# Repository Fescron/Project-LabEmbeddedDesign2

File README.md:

# Project-LabEmbeddedDesign2

<br/>

This repository contains the **presentation**, **reports** and **code** for the project constructed for **Embedded System Design 2 - Lab**.

<br/>

## 1 - Quick links

- [**Reports and presentation**](documentation/reports)
- [General important Doxygen documentation](https://fescron.github.io/Project-LabEmbeddedDesign2/index.html)
- [Doxygen code documentation of individual files and methods](https://fescron.github.io/Project-LabEmbeddedDesign2/files.html)
- [Code for the custom TTN decoder](software/decoder.js)
- [Schematic of custom PCB](documentation/schematics/project-embeddedSystemDesign2.pdf)
- [Schematic of DRAMCO LoRaWAN shield](documentation/schematics/dramco-LoRa-addon-schematic-v4-0.pdf)
- [Picture with PCB dimensions](hardware/project-embeddedSystemDesign2/3d-renders/project-embeddedSystemDesign2-pcb-dimensions.png)
- [The Things Network - Applications](https://console.thethingsnetwork.org/applications/)
- [Cayenne Dashboard](https://cayenne.mydevices.com/cayenne/dashboard/start)

<br/>

## 2 - GIT repo structure

|  Location  |  Content  |
| ---------- | --------- |
| [/docs/](https://fescron.github.io/Project-LabEmbeddedDesign2/index.html) | **[Doxygen](http://www.doxygen.org) code documentation.** |
| <br/>      |           |
| [/documentation/current measurements/](documentation/current%20measurements) | Documents containing current measurements. |
| [/documentation/current measurements/measurements-SF/](documentation/current%20measurements/measurements-SF) | Pictures depicting current profiles for sending 6 measurements at full gain with different LoraWAN *Spreading Factors*. More information can be found in section *"3 - LoRaWAN spreading factor (RN2483)"* in [this](documentation/current%20measurements/currents-2-projectEmbeddedDesign2.pdf) file . |
| <br/>      |           |
| [/documentation/datasheets/](documentation/datasheets) | General datasheets regarding the used items. |
| [/documentation/datasheets/hardware-design/](documentation/datasheets/hardware-design) | Documents regarding hardware design for the `EFM32HG` microcontroller. |
| [/documentation/datasheets/timers-energy-rtc/](documentation/datasheets/timers-energy-rtc) | Documents regarding `timers`, the `RTC` and `energy modes` on the `EFM32HG` microcontroller. |
| <br/>      |           |
| [/documentation/figures/](documentation/figures) | Figures used in reports and the README. |
| [/documentation/figures/installation/](documentation/figures/installation) | **Pictures taken during the project installation.** |
| [/documentation/reports/](documentation/reports) | **Reports and presentation.** |
| [/documentation/schematics/](documentation/schematics) | Schematics. <br/>  See [this](documentation/schematics/project-embeddedSystemDesign2.pdf) file for the schematic of the *self designed PCB* and [this](documentation/schematics/dramco-LoRa-addon-schematic-v4-0.pdf) file for the schematic of the *DRAMCO LoRaWAN shield*.
| <br/>      |           |
| [/hardware/project-embeddedSystemDesign2/](hardware/project-embeddedSystemDesign2) | [KiCad](http://kicad-pcb.org/) PCB design files. <br/> See [this](hardware/project-embeddedSystemDesign2/pdf/project-embeddedSystemDesign2.pdf) file for the *schematic* and [this](hardware/project-embeddedSystemDesign2/bom/bom-custom-gecko-v1-0.pdf) file for the *BOM*. |
| [/hardware/project-embeddedSystemDesign2/3d-renders/](hardware/project-embeddedSystemDesign2/3d-renders) | Pictures of 3D renders of the *self designed PCB*. <br/> On [this](hardware/project-embeddedSystemDesign2/3d-renders/project-embeddedSystemDesign2-pcb-dimensions.png) picture the *dimensions* are displayed. <br/>  [This](hardware/project-embeddedSystemDesign2/3d-renders/project-embeddedSystemDesign2.png) is a render of the *front* and [this](hardware/project-embeddedSystemDesign2/3d-renders/project-embeddedSystemDesign2-back.png) is a render of the *back*. |
| <br/>      |           |
| [/software/EFM32HG-Embedded2-project/](software/EFM32HG-Embedded2-project) | **Code for the project.** <br/> See [this](https://fescron.github.io/Project-LabEmbeddedDesign2/index.html) page for *general important documentation* and [this](https://fescron.github.io/Project-LabEmbeddedDesign2/files.html) page for information regarding *individual files and their methods*. [This](software/decoder.js) is the *decoder* for use on The *Things Network*. |

<br/>

## 3 - Code flow

**Note:** The code is developed using `Simplicity Studio v4` on `Ubuntu 18.04 LTS`. The code also has [dbprint](https://github.com/Fescron/dbprint) functionality.

**Extra notes on the flowchart:**

- **(\*1):** The following things get initialized:
    - Chip
    - GPIO wakeup (buttons & ADXL INT1)
    - ADC
    - Disable RN2483
    - Accelerometer (initialize SPI and use it to configure the accelerometer
- **(\*2):** On every external temperature measurement the VDD and DATA pin get re-configured. The oneWire protocol is achieved using *bit-banging*.
- **(\*3):** The RN2483 module gets enabled and configured before sending the data. Afterwards it gets disabled again. The **status** message is always send, measurements only if there are any recorded.
- **(\*4):** Only one set of measurements are send along with the status message.
- **(\*5):** The value of **X** depends on a configured setting.
- **(\*6):** A status message is send along with any recorded measurements.

<br/>

- Before entering a *sleep* state **all GPIO (data) pins are disabled** so they can't consume any power.
- **Clocks and peripherals** are only enabled when necessary.
- If an **error** occures this gets **forwarded to the cloud using a LoRaWAN status message**.
- To conserve sended bytes a **custom data-format** was used (along with a *decoder*).
- Negative internal and external temperatures were successfully send and displayed. The internal temperature seems to be 2 - 3 °C off.

<br/>

## 4 - Extra hardware changes

The [schematic](hardware/project-embeddedSystemDesign2/pdf/project-embeddedSystemDesign2.pdf) for the custom PCB **misses two resistors**. A surface mount `10 kΩ` resistor was added between the *data* and *power* pin for the DS18B20 temperature sensor. A `3,3 kΩ` resistor with wires was added between the `BREAK_1`pin and `VDD`. These added resistors can be seen on the bottom right on the left most picture below.

An **SMA connector for an external antenna** was also added to the DRAMCO LoRaWAN shield. This was done by **removing** the `chip-antenna`, capacitors `C3` and `C4` and inductor `L1` and replacing it with an SMA connector directly connected to the signal pin of the *RN2483* module. This modification can be seen on the right on the right most picture above.

To protect the PCB's from moisture and other contaminants, they were given 2 coats of `PLASTIK 70`.

<br/>

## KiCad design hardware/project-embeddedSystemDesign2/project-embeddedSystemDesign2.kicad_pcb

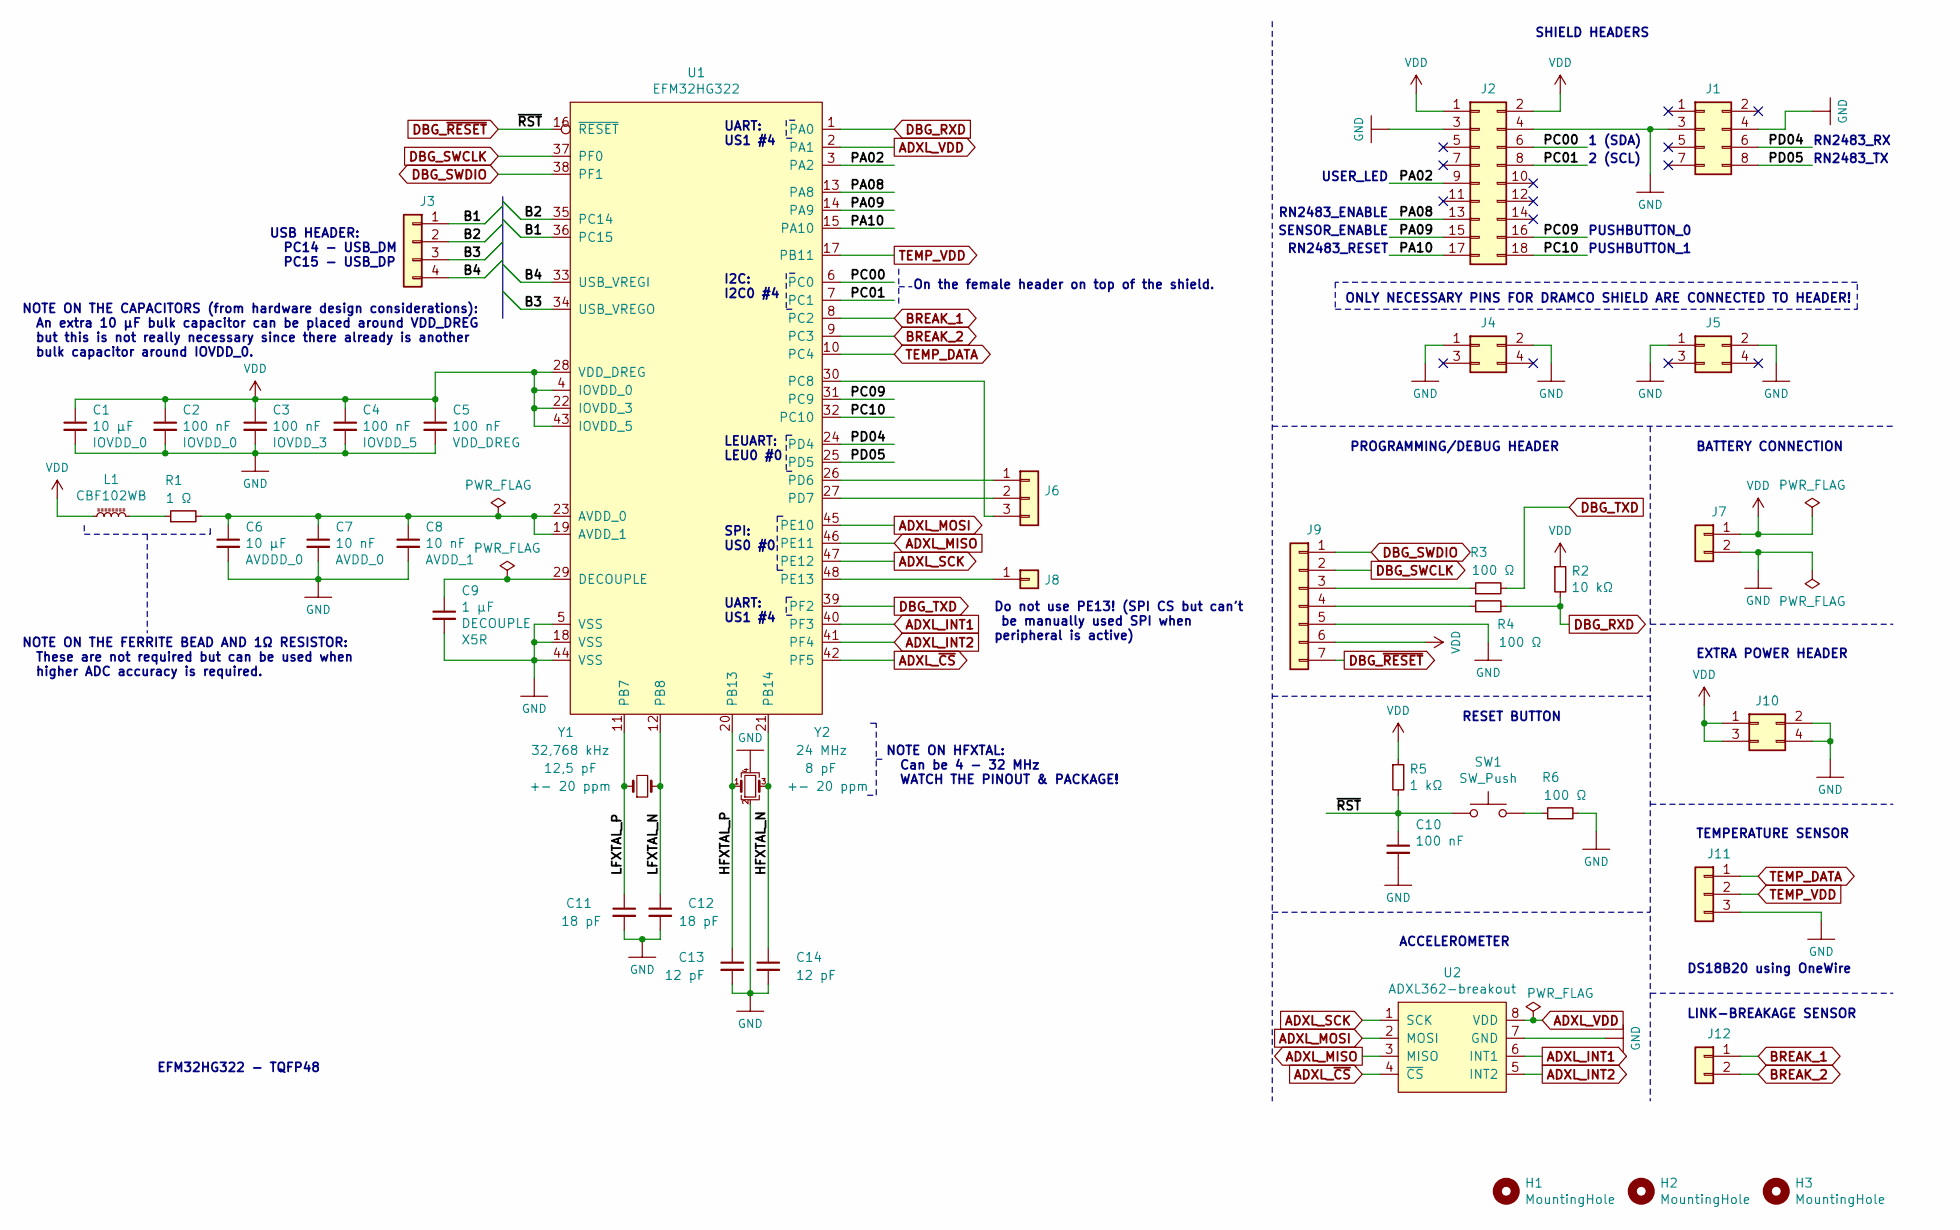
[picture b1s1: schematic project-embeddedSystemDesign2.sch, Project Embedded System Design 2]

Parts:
C1, C6: 10 µF; C_0805_2012Metric_Pad1.15x1.40mm_HandSolder
C2, C3, C4, C5, C10: 100 nF; C_0805_2012Metric_Pad1.15x1.40mm_HandSolder
C7, C8: 10 nF; C_0805_2012Metric_Pad1.15x1.40mm_HandSolder
C9: 1 µF; C_0805_2012Metric_Pad1.15x1.40mm_HandSolder
C11, C12: 18 pF; C_0805_2012Metric_Pad1.15x1.40mm_HandSolder
C13, C14: 12 pF; C_0805_2012Metric_Pad1.15x1.40mm_HandSolder
H1, H2, H3: MountingHole; MountingHole_3mm
J1: Conn_02x04_Odd_Even; PinHeader_2x04_P2.54mm_Vertical
J2: Conn_02x09_Odd_Even; PinHeader_2x09_P2.54mm_Vertical
J3: Conn_01x04; 1X04_LOCK
J4, J5: Conn_02x02_Odd_Even; PinHeader_2x02_P2.54mm_Vertical
J6, J11: Conn_01x03; 1X03_LOCK
J7: Conn_01x02; PinHeader_1x02_P2.54mm_Horizontal
J8: Conn_01x01; 1X01
J9: Conn_01x07; 1X07_LOCK
J10: Conn_02x02_Odd_Even; PinSocket_2x02_P2.54mm_Vertical
J12: Conn_01x02; 1X02_LOCK
L1: CBF102WB; L_0603_1608Metric_Pad1.05x0.95mm_HandSolder
R1: 1 Ω; R_0805_2012Metric_Pad1.15x1.40mm_HandSolder
R2: 10 kΩ; R_0805_2012Metric_Pad1.15x1.40mm_HandSolder
R3, R4, R6: 100 Ω; R_0805_2012Metric_Pad1.15x1.40mm_HandSolder
R5: 1 kΩ; R_0805_2012Metric_Pad1.15x1.40mm_HandSolder
SW1: SW_Push; SW_SPST_FSMSM
U1: EFM32HG322; LQFP-48_7x7mm_P0.5mm
U2: ADXL362-breakout; DIP-8_W10.16mm
Y1: 32,768 kHz; Crystal_SMD_2012-2Pin_2.0x1.2mm_HandSoldering; Tolerance +- 20 ppm
Y2: 24 MHz; CRYSTAL-SMD-5X3.2-4PAD; Tolerance +- 20 ppm

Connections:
/B1: J3.1, U1.36 (PC15)
/B2: J3.2, U1.35 (PC14)
/B3: J3.3, U1.34 (USB_VREGO)
/B4: J3.4, U1.33 (USB_VREGI)
/HFXTAL_N: C14.1, U1.21 (PB14), Y2.3
/HFXTAL_P: C13.1, U1.20 (PB13), Y2.1
/LFXTAL_N: C12.1, U1.12 (PB8), Y1.2
/LFXTAL_P: C11.1, U1.11 (PB7), Y1.1
/PA02: J2.9, U1.3 (PA2)
/PA08: J2.13, U1.13 (PA8)
/PA09: J2.15, U1.14 (PA9)
/PA10: J2.17, U1.15 (PA10)
/PC00: J2.6, U1.6 (PC0)
/PC01: J2.8, U1.7 (PC1)
/PC09: J2.16, U1.31 (PC9)
/PC10: J2.18, U1.32 (PC10)
/PD04: J1.6, U1.24 (PD4)
/PD05: J1.8, U1.25 (PD5)
ADXL_INT1: U1.40 (PF3), U2.6 (INT1)
ADXL_INT2: U1.41 (PF4), U2.5 (INT2)
ADXL_MISO: U1.46 (PE11), U2.3 (MISO)
ADXL_MOSI: U1.45 (PE10), U2.2 (MOSI)
ADXL_SCK: U1.47 (PE12), U2.1 (SCK)
ADXL_VDD: U1.2 (PA1), U2.8 (VDD)
ADXL_~CS: U1.42 (PF5), U2.4 (~CS)
BREAK_1: J12.1, U1.8 (PC2)
BREAK_2: J12.2, U1.9 (PC3)
DBG_RXD: R2.2, R4.2, U1.1 (PA0)
DBG_SWCLK: J9.2, U1.37 (PF0)
DBG_SWDIO: J9.1, U1.38 (PF1)
DBG_TXD: R3.2, U1.39 (PF2)
DBG_~RESET: C10.1, J9.7, R5.2, SW1.1, U1.16 (~RESET); also elsewhere on the board
GND: C1.2, C2.2, C3.2, C4.2, C5.2, C6.2, C7.2, C8.2, C9.2, C10.2, C11.2, C12.2, C13.2, C14.2, J1.3, J1.4, J2.3, J2.4, J4.1, J4.2, J5.1, J5.2, J7.2, J9.5, J10.2, J10.4, J11.3, R6.2, U1.5 (VSS), U1.18 (VSS), U1.44 (VSS), U2.7 (GND), Y2.2, Y2.4
unnamed: C6.1, C7.1, C8.1, R1.2, U1.19 (AVDD_1), U1.23 (AVDD_0)
unnamed: C9.1, U1.29 (DECOUPLE)
unnamed: J6.1, U1.26 (PD6)
unnamed: J6.2, U1.27 (PD7)
unnamed: J6.3, U1.30 (PC8)
unnamed: J8.1, U1.48 (PE13)
unnamed: J9.3, R3.1
unnamed: J9.4, R4.1
unnamed: L1.2, R1.1
unnamed 42: R6.1, SW1.2; also elsewhere on the board
TEMP_DATA: J11.1, U1.10 (PC4)
TEMP_VDD: J11.2, U1.17 (PB11)
VDD: C1.1, C2.1, C3.1, C4.1, C5.1, J2.1, J2.2, J7.1, J9.6, J10.1, J10.3, L1.1, R2.1, R5.1, U1.4 (IOVDD_0), U1.22 (IOVDD_3), U1.28 (VDD_DREG), U1.43 (IOVDD_5)

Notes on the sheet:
SHIELD HEADERS
PROGRAMMING/DEBUG HEADER
ACCELEROMETER
TEMPERATURE SENSOR
DS18B20 using OneWire
LINK-BREAKAGE SENSOR
RESET BUTTON
BATTERY CONNECTION
Do not use PE13! (SPI CS but can't be manually used SPI when peripheral is active)
EXTRA POWER HEADER
SPI: US0 #0
UART: US1 #4
I2C: I2C0 #4
LEUART: LEU0 #0
NOTE ON HFXTAL: Can be 4 - 32 MHz WATCH THE PINOUT & PACKAGE!
NOTE ON THE CAPACITORS (from hardware design considerations): An extra 10 µF bulk capacitor can be placed around VDD_DREG but this is not really necessary since there already is another bulk capacitor around IOVDD_0.
NOTE ON THE FERRITE BEAD AND 1Ω RESISTOR: These are not required but can be used when higher ADC accuracy is required.
EFM32HG322 - TQFP48
USB HEADER: PC14 - USB_DM PC15 - USB_DP
ONLY NECESSARY PINS FOR DRAMCO SHIELD ARE CONNECTED TO HEADER!
USER_LED
RN2483_ENABLE
SENSOR_ENABLE
RN2483_RESET
PUSHBUTTON_0
PUSHBUTTON_1
RN2483_RX
RN2483_TX
1 (SDA)
2 (SCL)
On the female header on top of the shield.

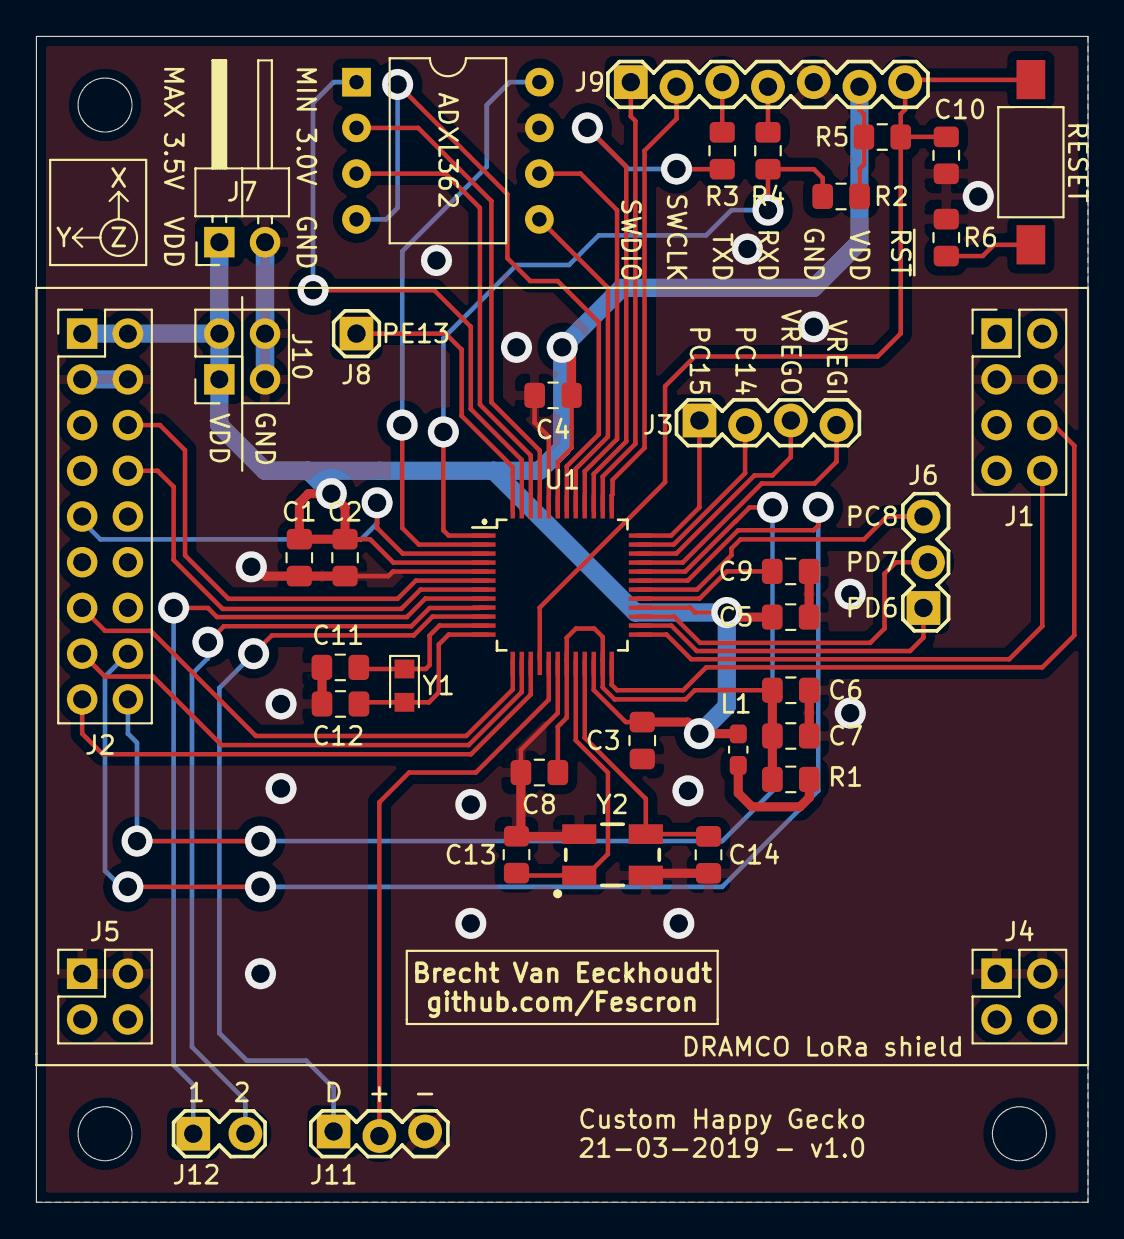
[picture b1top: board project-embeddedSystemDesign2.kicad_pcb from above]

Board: 2 copper layers, 58.4 x 64.8 mm, 41 parts (0 on the bottom side), 46 nets.

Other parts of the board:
RESET: SW_Push; SW_SPST_FSMSM

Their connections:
DBG_~RESET: RESET.1; also elsewhere on the board
unnamed 42: RESET.2; also elsewhere on the board

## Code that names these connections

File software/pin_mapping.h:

/***************************************************************************//**
 * @file pin_mapping.h
 * @brief The pin definitions for the custom Happy Gecko board.
 * @version 1.0
 * @author Brecht Van Eeckhoudt
 ******************************************************************************/


/* Include guards prevent multiple inclusions of the same header */
#ifndef _PIN_MAPPING_H_
#define _PIN_MAPPING_H_

#include <em_gpio.h>


/* ADXL362 */
#define ADXL_SPI            USART0
#define ADXL_SPI_LOC        0
#define ADXL_MOSI_PORT      gpioPortE
#define ADXL_MOSI_PIN       10
#define ADXL_MISO_PORT      gpioPortE
#define ADXL_MISO_PIN       11
#define ADXL_CLK_PORT       gpioPortE
#define ADXL_CLK_PIN        12
#define ADXL_NCS_PORT       gpioPortF 	/* Can't use the US0_CS port (PE13) to manually set/clear CS line */
#define ADXL_NCS_PIN        5

#define ADXL_INT1_PORT      gpioPortF
#define ADXL_INT1_PIN       3
#define ADXL_INT2_PORT      gpioPortF
#define ADXL_INT2_PIN       4
#define ADXL_VDD_PORT       gpioPortA
#define ADXL_VDD_PIN        1

/* LED */
#define LED_PORT            gpioPortA
#define LED_PIN             2

/* Buttons */
#define PB0_PORT            gpioPortC
#define PB0_PIN             9
#define PB1_PORT            gpioPortC
#define PB1_PIN             10

/* UART */
#define DBG_UART            USART1
#define DBG_UART_LOC        4
#define DBG_TXD_PORT        gpioPortF
#define DBG_TXD_PIN         2
#define DBG_RXD_PORT        gpioPortA
#define DBG_RXD_PIN         0

/* DS18B20 */
#define TEMP_DATA_PORT      gpioPortC
#define TEMP_DATA_PIN       4
#define TEMP_VDD_PORT       gpioPortB
#define TEMP_VDD_PIN        11

/* Link breakage sensor */
#define BREAK1_PORT         gpioPortC
#define BREAK1_PIN          2
#define BREAK2_PORT         gpioPortC
#define BREAK2_PIN          3

/* RN2483 */
#define RN2483_UART         LEUART0
#define RN2483_UART_LOC     0
#define RN2483_TX_PORT      gpioPortD
#define RN2483_TX_PIN       4
#define RN2483_RX_PORT      gpioPortD
#define RN2483_RX_PIN       5
#define RN2483_RESET_PORT   gpioPortA
#define RN2483_RESET_PIN    10

/* External header */
#define IIC_SDA_PORT        gpioPortC
#define IIC_SDA_PIN         0
#define IIC_SCL_PORT        gpioPortC
#define IIC_SCL_PIN         1

/* Power supply enable */
#define PM_RN2483_PORT		gpioPortA
#define PM_RN2483_PIN		8
#define PM_SENS_EXT_PORT	gpioPortA
#define PM_SENS_EXT_PIN		9


#endif /* _PIN_MAPPING_H_ */

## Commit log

2019-03-21 Add datasheets
2019-03-21 Change file structure
2019-03-22 Add PCB design files
2019-03-23 Update PCB
2019-03-23 Update BOM
2019-03-23 Add pinmap
2019-03-24 Upload reference manual
2019-03-25 Update PCB gerbers
2019-03-27 Add current estimates
2019-03-28 Fix typo
2019-03-31 Upload working code
2019-03-31 Remove unnecessary file
2019-03-31 .gitignore is now working
2019-04-01 Start removing unnecessary DOUT GPIO things
2019-04-01 More DOUT GPIO cleanup
2019-04-01 Debug DOUT argument and remove some unnecessary lines accordingly
2019-04-02 Remove unnecessary files, start adding link break sensor, cleanup code
2019-04-04 Start adding delay methods which put the MCU to EM1 or EM2 using RTCC
2019-04-04 Moved delay functionality from "util" to "delay", updated documentation
2019-04-04 Made some methods/global variables static, fixed some debug printing
2019-04-06 Reworked delay functionality, updated documentation & include locations
2019-04-06 Updated method names, renamed file, disabled clocks when possible
2019-04-06 Made more methods static, removed dbprint in IRQhandlers, updated checks
2019-04-07 Updated documentation
2019-04-07 Updated documentation, started implementing state-machine
2019-04-07 Added readVBAT function, cleaned up includes and documentation
2019-04-08 Implemented ULFRCO delay functionality, updated documentation
2019-04-08 Fixed Doxygen documentation and included it in upload
2019-04-08 Changed gitignore and uploaded HTML files
2019-04-08 Move doxygen output to docs folder
2019-04-08 Added readme with permalink
2019-04-08 Remove readme.md in docs folder
2019-04-08 Update documentation
2019-04-08 Update doxygen documentation
2019-04-08 Update doxygen again
2019-04-08 Update doxygen
2019-04-08 Update doxygen with new settings
2019-04-08 Update doxygen files with new settings
2019-04-08 Update doxygen files with inline source info
2019-04-08 Update doxygen files with new sorting order
2019-04-08 Update doxygen files with new index sort order
2019-04-08 Another doxygen settings update
2019-04-08 Update doxygen with new theme
2019-04-08 Update doxygen theme
2019-04-08 Add regular doxygen documentation
2019-04-08 Add regular doxygen documentation theme
2019-04-08 Go back to regular doxygen theme
2019-04-09 Updated documentation and define checks
2019-04-09 Upload reports
2019-04-13 Added extra ADC functionality, updated inc, started changing temp logic
2019-04-13 Updated doxygen documentation
2019-04-13 Added extra ADC functionality, updated incs, started changing temp logic
2019-04-15 Upload PCB with dimensions
2019-04-15 Updated BOM
2019-04-15 Update current estimates
2019-04-17 Started using working DS18B20 code
2019-04-19 Fixed cable checking method, started checking hourly wakeup timing
2019-04-20 Added struct to keep data, used custom enums for config methods
2019-04-20 Removed unnecessary INT checks, cleaned up ADC code
2019-04-20 Fixed "sleep" current but broke read temperature functionality
2019-04-21 Cleaned up documentation, added ADXL testing functionality
2019-04-25 Added documentation about GPIO/DATA pins and sleeping
2019-04-25 Disabled clocks when not in use and added RTC wakeup logic
2019-04-25 Stopped disabling RTC timer on pin wakeup
2019-04-25 Updated doculentation
2019-04-25 Added functionality to detect a "storm"
2019-04-25 Only enabled timer clocks when in use
2019-04-28 Added LoRaWAN functionality
2019-04-28 Added additional state
2019-04-28 Modified delay logic
2019-04-29 Started using new LoRaWAN sending methods to use less bytes
2019-04-30 Updated error numbering and documentation
2019-04-30 Changed project name
2019-04-30 Moved some definitions from header to source file
2019-04-30 Added method to send data following the regular LPP format
2019-04-30 Updated settings
2019-04-30 Updated return type of temperature reading method
2019-04-30 Implemented error method to forward value to the cloud
2019-04-30 Added extra I2C definitions
2019-04-30 Updated error number, added enable/disable functionality for LED
2019-05-01 Added basic timeout functionality
2019-05-01 Updated timeout functionality and changed returntype
2019-05-01 Changed types
2019-05-01 Started fixing timeout functionality and changed returntypes
2019-05-01 Added debug info
2019-05-01 Fixed error forwarding functionality
2019-05-01 Added documentation
2019-05-01 Updated with new methods
2019-05-03 Move files from "system" to "lora"
2019-05-03 Update timeout and dbprint functionality
2019-05-03 Update dbprint functionality
2019-05-03 Update dbprint and configuration functionality
2019-05-03 Move more functionality to this file
2019-05-03 Update dbprint and timeout functionality and fix temperature reading
2019-05-03 Remove unnecessary variables and definitions
2019-05-03 Update functionality according to underlying methods
2019-05-06 Fixed data.index clearing (previous code wrote data out of given array)
2019-05-06 Changed so that no code will be executed further if first INIT failed
2019-05-07 Added license information
2019-05-07 Added license
2019-05-07 Updated version number
2019-05-07 Updated documentation and version number
2019-05-07 Added functionality around "error" calls and updated version number
2019-05-07 Added functionality to send measurements on cable breaking detection
2019-05-07 Added code to check passed sleep time and around "error" calls
2019-05-07 Updated code to reflect underlying changes
2019-05-08 Started to add release configuration
2019-05-08 Cleaned up file and updated version number
2019-05-08 Added figures
2019-05-08 Added SF testing figures
2019-05-08 Added battery datasheets
2019-05-09 Added current measurements
2019-05-09 Added RN2483 datasheet
2019-05-10 Added flowchart
2019-05-17 Cropped 3D renders
2019-05-18 Added presentation
2019-05-18 Added code for TTN decoder
2019-05-18 Fixed spacing in decoder code
2019-05-23 Updated sleep logic when waking up using the accelerometer
2019-05-31 Added final report
2019-05-31 Added extra pictures
2019-05-31 Updated wakeup-timing to 30 minutes instead of 10
2019-09-30 Added dbprint's files instead of linking to work as standalone project
2019-09-30 Chanced logic to clear the buffer before going to sleep to fix bug
2019-09-30 Changed timing
2019-09-30 Updated cache
2019-10-01 Removed @mainpage from dbprint_documentation.h
2019-10-03 Stopped using an external global variable in dbprint
2019-10-03 Added comment about supposed problem with dbpointer
2019-10-03 Added extra ISR handlers
2019-10-03 Updated version number with added ISR's
2019-10-04 Removed `static` before the local variables (not necessary).
2019-10-04 Increased RN2483_COMMANDBUFFER_SIZE to fix memory overwriting bug
2019-10-07 Moved `msTicks` variable and systick handler in `#if` check
2021-09-03 Updated output path

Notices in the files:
README.md:
License: GNU GPL v3.0
